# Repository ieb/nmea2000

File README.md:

This repository contains a number of utilities generally aimed at interfacing with a NMEA2000 CAN bus and collecting stats in InfluxDB for analysis in Grafana.

The repository is mainly to keep a record of work in progress, rather than a neat and tidy implementation, but if it helps others, great.

The code runs on an Arduino Due with a CAN bus trancever.
Some code may also run on an Arduino Mega to simulate Raymarine wind, speed and temperature sensors.
The heavy lifting on the Arduino as been done by https://github.com/ttlappalainen/NMEA2000.git to use the code here on a Due you may also need
https://github.com/collin80/due_can.git https://github.com/ttlappalainen/NMEA2000_due.git which the NMEA2000 implementation and CAN Bus drivers for the Due. 

* libs contains c++ code for the ArduinoDue
** batteryMonitor.h - monitoring batteries and current using Hall Effect sensors on ADC pins.
** boarMonitor.h - emitting boat speed, wind speed data as NMEA2000 PGNs
** enviroMonitor.h - monitoring pressure and temperature
** events.h - an event queue.
** monitors.h - constants
** motionSensor.h - rotation, acceleration sensor
** multiSensor.h - wind and water speed sensor with corrections for motion etc, also calculates 
** pogo1250.h - Data for a pogo1250 polar.
** polar.h - polar performance calculations.
** statistics.h - stats for linear and radial data.
** testmocks.h - mocks to allow tests to run.
** waterMonitor.h - water temp sensor.
* monitorAndBridge contains a sensor monitor and bridge from a NMEA2000 bus to ActisenseSerial, with the ability to read the raw signals from Airmar water speed and RayMarine WindSensorts, battery voltages and a 10DoF sensor board. There is a built in polar performance monitor that emits % polar performance and target boat speed.

The Marine instrument installation is a Raymarine SeatalkNG installation with a e7 MFD, althogh there is nothing here that is specific to Raymarine. At the electrical and protocol level SeatalkNG == NMEA2000 == CAN@250kb/s. The differences are physical, mainly to ease installation.

As well as emitting CAM messages onto the NMEA2000 bus the Arduino Due runs code to implement sufficient of the Actisense protocol to feed SignalK running on a Pi Zero W. Installation of that part is listed below. Most of this is achieved with confgiguration and no additional code.

# Pi Zero W installation - Rough notes.

Installation on a Pi Zero W for pushing stats from NMEA2000 -> Arduino Due -> SkignalK -> InfluxDB -> Grafana

Using Raspbain Lite written to a SDMicro card boot and configure the Pi Zero W, once booted. At the console (HDMI+USB Keyboard)

## Setup wifi as root
    
    cat << EOF > /etc/wpa_supplicant/wpa_supplicant.conf 
    country=GB
    ctrl_interface=DIR=/var/run/wpa_supplicant GROUP=netdev
    update_config=1
    network={
         ssid="yourSSID"
         psk="*********"
    }
    EOF

## TODO: setup as a Access Point, assuming it can be done, if not make the MFD the access point and join that network.

## Enable SSH

    raspi-config
    # then enable ssh server

## reboot to get the wifi up.

Now switch to using ssh in from a Linux box.

## install signalK requirements all as root

    apt-get update
    apt-get install -y curl git build-essential libnss-mdns avahi-utils libavahi-compat-libdnssd-dev
    cd /opt/
//    wget https://nodejs.org/dist/v6.10.2/node-v6.10.2-linux-armv6l.tar.xz
    wget https://nodejs.org/dist/v6.11.1/node-v6.11.1-linux-armv6l.tar.gz 
    tar xvzf node-v6.11.1-linux-armv6l.tar.gz  
    rm node-v6.11.1-linux-armv6l.tar.gz 
    cd /usr/local/bin/
    ln -s /opt/node-v6.11.1-linux-armv6l/bin/* .

## Install InfluxDB as root
    cd 
    wget http://ftp.us.debian.org/debian/pool/main/i/influxdb/influxdb_1.1.1+dfsg1-4_armhf.deb
    wget http://ftp.us.debian.org/debian/pool/main/i/influxdb/influxdb-client_1.1.1+dfsg1-4_armhf.deb
    dpkg -i influxdb_1.1.1+dfsg1-4_armhf.deb
    dpkg -i influxdb-client_1.1.1+dfsg1-4_armhf.deb
    apt-get install -f

## Install Grafana as root

    wget https://bintray.com/fg2it/deb-rpi-1b/download_file?file_path=main%2Fg%2Fgrafana_4.2.0_armhf.deb
    mv download_file\?file_path\=main%2Fg%2Fgrafana_4.2.0_armhf.deb grafana_4.2.0_armhf.deb
    dpkg -i grafana_4.2.0_armhf.deb 
    systemctl daemon-reload
    systemctl enable grafana-server
    systemctl start grafana-server

## Install collectd to get stats on the OS into InfluxDB

This will allow you to see if the Pi Zero is overloaded. 

    apt-get install collectd

Edit collectd to disable rrdtool, battery and irq plugins, removing the config sections.
Enable network and add the following

    <Plugin network>
          Server "127.0.0.1" "8096"
    </Plugin>

Edit /etc/influxdb/influxdb.conf to enable collectd

    [[collectd]]
      enabled = true
      bind-address = ":8096"
      database = "collectd"
      typesdb = "/usr/share/collectd/types.db"

Check that /usr/share/collectd/types.db exists  (if not its at https://github.com/collectd/collectd/blob/master/src/types.db)

    service influxdb restart
    service collectd restart

Check all is Ok

    service influxdb status
    service collectd status
    service grafana-server status

## Complete SignalK installation

As a normal user who is a member of the staff group

    cd /usr/local/src
    git clone https://github.com/SignalK/signalk-server-node.git
    cd signalk-server-node
    npm install     # Wait for some time as everything gets installed.
    npm install mdns
    sudo bash rpi-setup.sh

use port 80 to run SignalK see https://github.com/SignalK/signalk-server-node/blob/master/raspberry_pi_installation.md for more detailed info

## Add reporting to InfluxDB

    cd /usr/local/src/signalk-server-node
    npm install https://github.com/sbender9/signalk-to-influxdb
    service signalk restart

check all ok 

    service signalk status 

Then go to http://localhost and configure the influxDB plugn

check all ok again

    service signalk status 

OS level info should now be in the collectd db, create a Grafana datasource pointing to that DB.
See OS Dashboard.json and windDashboard.json for exmaples.

The SignalK process will report to InfluxDB over the http API, which involves 1 POST oepration per report.
This is probably less overhead than reporting using the InfluxDB UDP route, but keep an eye on load average
and IO stats in Grafana (see OSDashboard.json for a Grafana Daskboard on the OS). Also see WindDashboard for 
a Dashboard on AWA etc.

## Connections

The Arduino is connected to the Pi using a USB Cable, the Arduino appears as a USB CDC Serial port at /dev/ttyACM0 which can be opened at 115200 baud. 

lsusb should show

    root@lunacore:/usr/local/src/signalk-server-node# lsusb
    Bus 001 Device 005: ID 2341:003d Arduino SA 
    Bus 001 Device 001: ID 1d6b:0002 Linux Foundation 2.0 root hub
    root@lunacore:/usr/local/src/signalk-server-node# 
    root@lunacore:/usr/local/src/signalk-server-node# usb-devices 

    T:  Bus=01 Lev=00 Prnt=00 Port=00 Cnt=00 Dev#=  1 Spd=480 MxCh= 1
    D:  Ver= 2.00 Cls=09(hub  ) Sub=00 Prot=01 MxPS=64 #Cfgs=  1
    P:  Vendor=1d6b ProdID=0002 Rev=04.04
    S:  Manufacturer=Linux 4.4.50+ dwc_otg_hcd
    S:  Product=DWC OTG Controller
    S:  SerialNumber=20980000.usb
    C:  #Ifs= 1 Cfg#= 1 Atr=e0 MxPwr=0mA
    I:  If#= 0 Alt= 0 #EPs= 1 Cls=09(hub  ) Sub=00 Prot=00 Driver=hub

    T:  Bus=01 Lev=01 Prnt=01 Port=00 Cnt=01 Dev#=  5 Spd=12  MxCh= 0
    D:  Ver= 1.10 Cls=02(commc) Sub=00 Prot=00 MxPS= 8 #Cfgs=  1
    P:  Vendor=2341 ProdID=003d Rev=00.01
    S:  Manufacturer=Arduino (www.arduino.cc)
    S:  Product=Arduino Due Prog. Port
    S:  SerialNumber=9543334393335111B181
    C:  #Ifs= 2 Cfg#= 1 Atr=c0 MxPwr=100mA
    I:  If#= 0 Alt= 0 #EPs= 1 Cls=02(commc) Sub=02 Prot=01 Driver=cdc_acm
    I:  If#= 1 Alt= 0 #EPs= 2 Cls=0a(data ) Sub=00 Prot=00 Driver=cdc_acm
    root@lunacore:/usr/local/src/signalk-server-node# 

Signak node server should be configured with an actisense input listening to this port, and should have plugins configured to 
a) send data to InfluxDB b) NMEA0183. Currently there are only plugins for TCP connections which causes a high level of 
turnover of TCP ports, it might be better to use UDP, that that will need some coding.

It is possible to power the Pi from the ArduinoDue over USB and visa versa. The Arduino uses < 100mA, but the Pi might use a bit more when under full load. 

# Update - September 2017

Sending data to influxDB on a standard SignalK setup swamps InfluxDB making it unusable, probably as a result of the frequency of packets > 1s in some cases, and the way the standard signalk-to-influxDB plugin is written. New signalk-telemetry plugin dixes this sending data in one block, queued to be more effcient at a fixed rate.

It may be possible to run everything from the Pi using socketCan rather than using a Due. This needs MCP2515 trancevers, 12C for the 10Dof sensor. In addition 1Wire temperature sensors and a I2C RTC can be added. Potentially this reduces power consumption as 80mA isnt needed to power the Due any more. the Pi has no A2D so a SPI based chip would need to be used.

The Pi supports 2x CAN trancevers with SocketCAN.

Raspberry Pi 10Dof

The npm module https://www.npmjs.com/package/nodeimu works for several 10DOf sensors on i2C, setup only requires i2c is enabled.
The IMU Requires configuration see https://github.com/RTIMULib/RTIMULib2 which also requires Octave to be installed for full calibration.

dtparam=i2c_arm=on

Raspberry Pi RTC
Disconnected from ntp the Pi will not keep time, using a ds3231 over i2c gives acurate time once setup.

dtoverlay=i2c-rtc,ds3231
see http://raspmer.blogspot.co.uk/2015/07/how-to-use-ds3231-i2c-real-time-clock.html

Raspberry Pi 1 Wire

DS18B20 are 1 wire temperature sensors. To read on a Pi enable 1wire and connedt with a 4K7 pullup to 3.3v, where the 1 wire is the default pin 7 

Output is at cat  /sys/bus/w1/devices/<ID>/w1_slave.
Map the ID to the sensor by warming each sensor in turn.

https://www.npmjs.com/package/ds18b20 for NPM

Raspberry Pi CanBus

Investigating how to run over SocketCan

2x MCP2515 drivers with Trancevers from eBay, MUST be connected with 3.3V to 5V level shifters to avoid GPIO damage as the trancevers will run at 5V. 2 can be connected to get CAN0 and CAN1

Wiring 

    2 5V   --------------- Vdd
    1 3V3   ------> LS 3V3
    2 5V ---------> LS 5V
    9 GND --------> LS GND
    9 GND  --------------  GND
    19 MOSI ---->  LS ----> SI0 & SI1
    21 MOSO <----  LS <---- SO0 & SO1
    23 SCLK ------> LS ----> SCLK0 & SCLK1
    24 CE0 ------> LS ----> CS0
    26 CE1 ------> LS ----> CS1
    18 GPIO24 <--  LS <---- INT0
    22 xGPIO25 <--  LS <---- INT1

    dtoverlay mcp2515-can0  oscillator=8000000 interrupt=24
    dtoverlay mcp2515-can1  oscillator=8000000 interrupt=25

    root@raspb:~/can-utils# dmesg | egrep "spi|can"
    [  477.594591] mcp251x spi0.0 can0: MCP2515 successfully initialized.
    [  487.165293] mcp251x spi0.1 can1: MCP2515 successfully initialized.
    [  495.704786] can: controller area network core (rev 20120528 abi 9)
    root@raspb:~/can-utils# ifconfig can0
    can0: flags=128<NOARP>  mtu 16
            unspec 00-00-00-00-00-00-00-00-00-00-00-00-00-00-00-00  txqueuelen 10  (UNSPEC)
            RX packets 0  bytes 0 (0.0 B)
            RX errors 0  dropped 0  overruns 0  frame 0
            TX packets 0  bytes 0 (0.0 B)
            TX errors 0  dropped 0 overruns 0  carrier 0  collisions 0

    root@raspb:~/can-utils# ifconfig can1
    can1: flags=128<NOARP>  mtu 16
            unspec 00-00-00-00-00-00-00-00-00-00-00-00-00-00-00-00  txqueuelen 10  (UNSPEC)
            RX packets 0  bytes 0 (0.0 B)
            RX errors 0  dropped 0  overruns 0  frame 0
            TX packets 0  bytes 0 (0.0 B)
            TX errors 0  dropped 0 overruns 0  carrier 0  collisions 0

    root@raspb:~/can-utils# 

Install can-utils from source.

    # git clone https://github.com/linux-can/can-utils.git
    # cd can-utils
    # ./autogen.sh
    # ./configure
    # make
    # sudo make install

If initialisation reports a wiring problem, then there almost cerainly is a wiring problem.

Configure interface

    root@raspb:~/can-utils# ip link set can0 up type can bitrate 250000
    root@raspb:~/can-utils#  ip link set can1 up type can bitrate 250000

Test

    root@raspb:~/can-utils# ./candump can1 &
    [1]+ ./candump can1 &
    root@raspb:~/can-utils# ./cansend can0 001#1122334455667788
      can1  001   [8]  11 22 33 44 55 66 77 88
    root@raspb:~/can-utils# ./cansend can0 001#1122334455667788
      can1  001   [8]  11 22 33 44 55 66 77 88
    root@raspb:~/can-utils# ./cansend can0 001#1122334455667788
      can1  001   [8]  11 22 33 44 55 66 77 88
    root@raspb:~/can-utils# 

To echo all CAN1 traffic to CAN0, setup CAN1 to listen only, and setup CAN0 to have loopback enabled to anything reading CAN0 gets the CAN0 messages as well.

    root@raspb:~/can-utils# ip link set can0 up type can bitrate 250000 loopback on
    root@raspb:~/can-utils#  ip link set can1 up type can bitrate 250000 listen-only on

Then to bridge

    candump can1 -B can0

For can0 -> SK

see https://github.com/chacal/signalk-socketcan-device

------------------------------------------------------

Moved back to the Due for now as its single threaded and doesnt stop expecially with no memory allocation. Processing power is a lot less, but it does a lot less also, not having an OS. 84MHz is plenty for this usage.

Todo:
Test polar calcs - partially done.
Test Can0 - done
Test IMU and calibrate - done.
Test Cos and Sin - done
Test Pulse counters  - done
Test SD card
Test 1 Wire
Test wind and speed calcs
Test linear voltage regulator vs noise from dc-dc converter 
   Linear voltage is no nose, but too hot
   LTSpice model indicates a 10uF cap will eliminate ripple from buck converter.

Input is candump can0 pipe, output is signalk-socketcan-device.

    "pipedProviders": [{
      "id": "can0",
      "pipeElements": [
        {
          "type": "providers/execute",
          "options": {
            "command": "candump can0 | candump2analyzer | analyzer -json -si -nv"
          }
        },
        {
          "type": "providers/liner"
        },
        {
          "type": "providers/from_json"
        },
        {
          "type": "signalk-socketcan-device",
          "options": {
            "n2kAddress": 110,
            "canDevice": "can0"
          }
        },
        {
          "type": "providers/n2k-signalk"
        }
      ]
    }]

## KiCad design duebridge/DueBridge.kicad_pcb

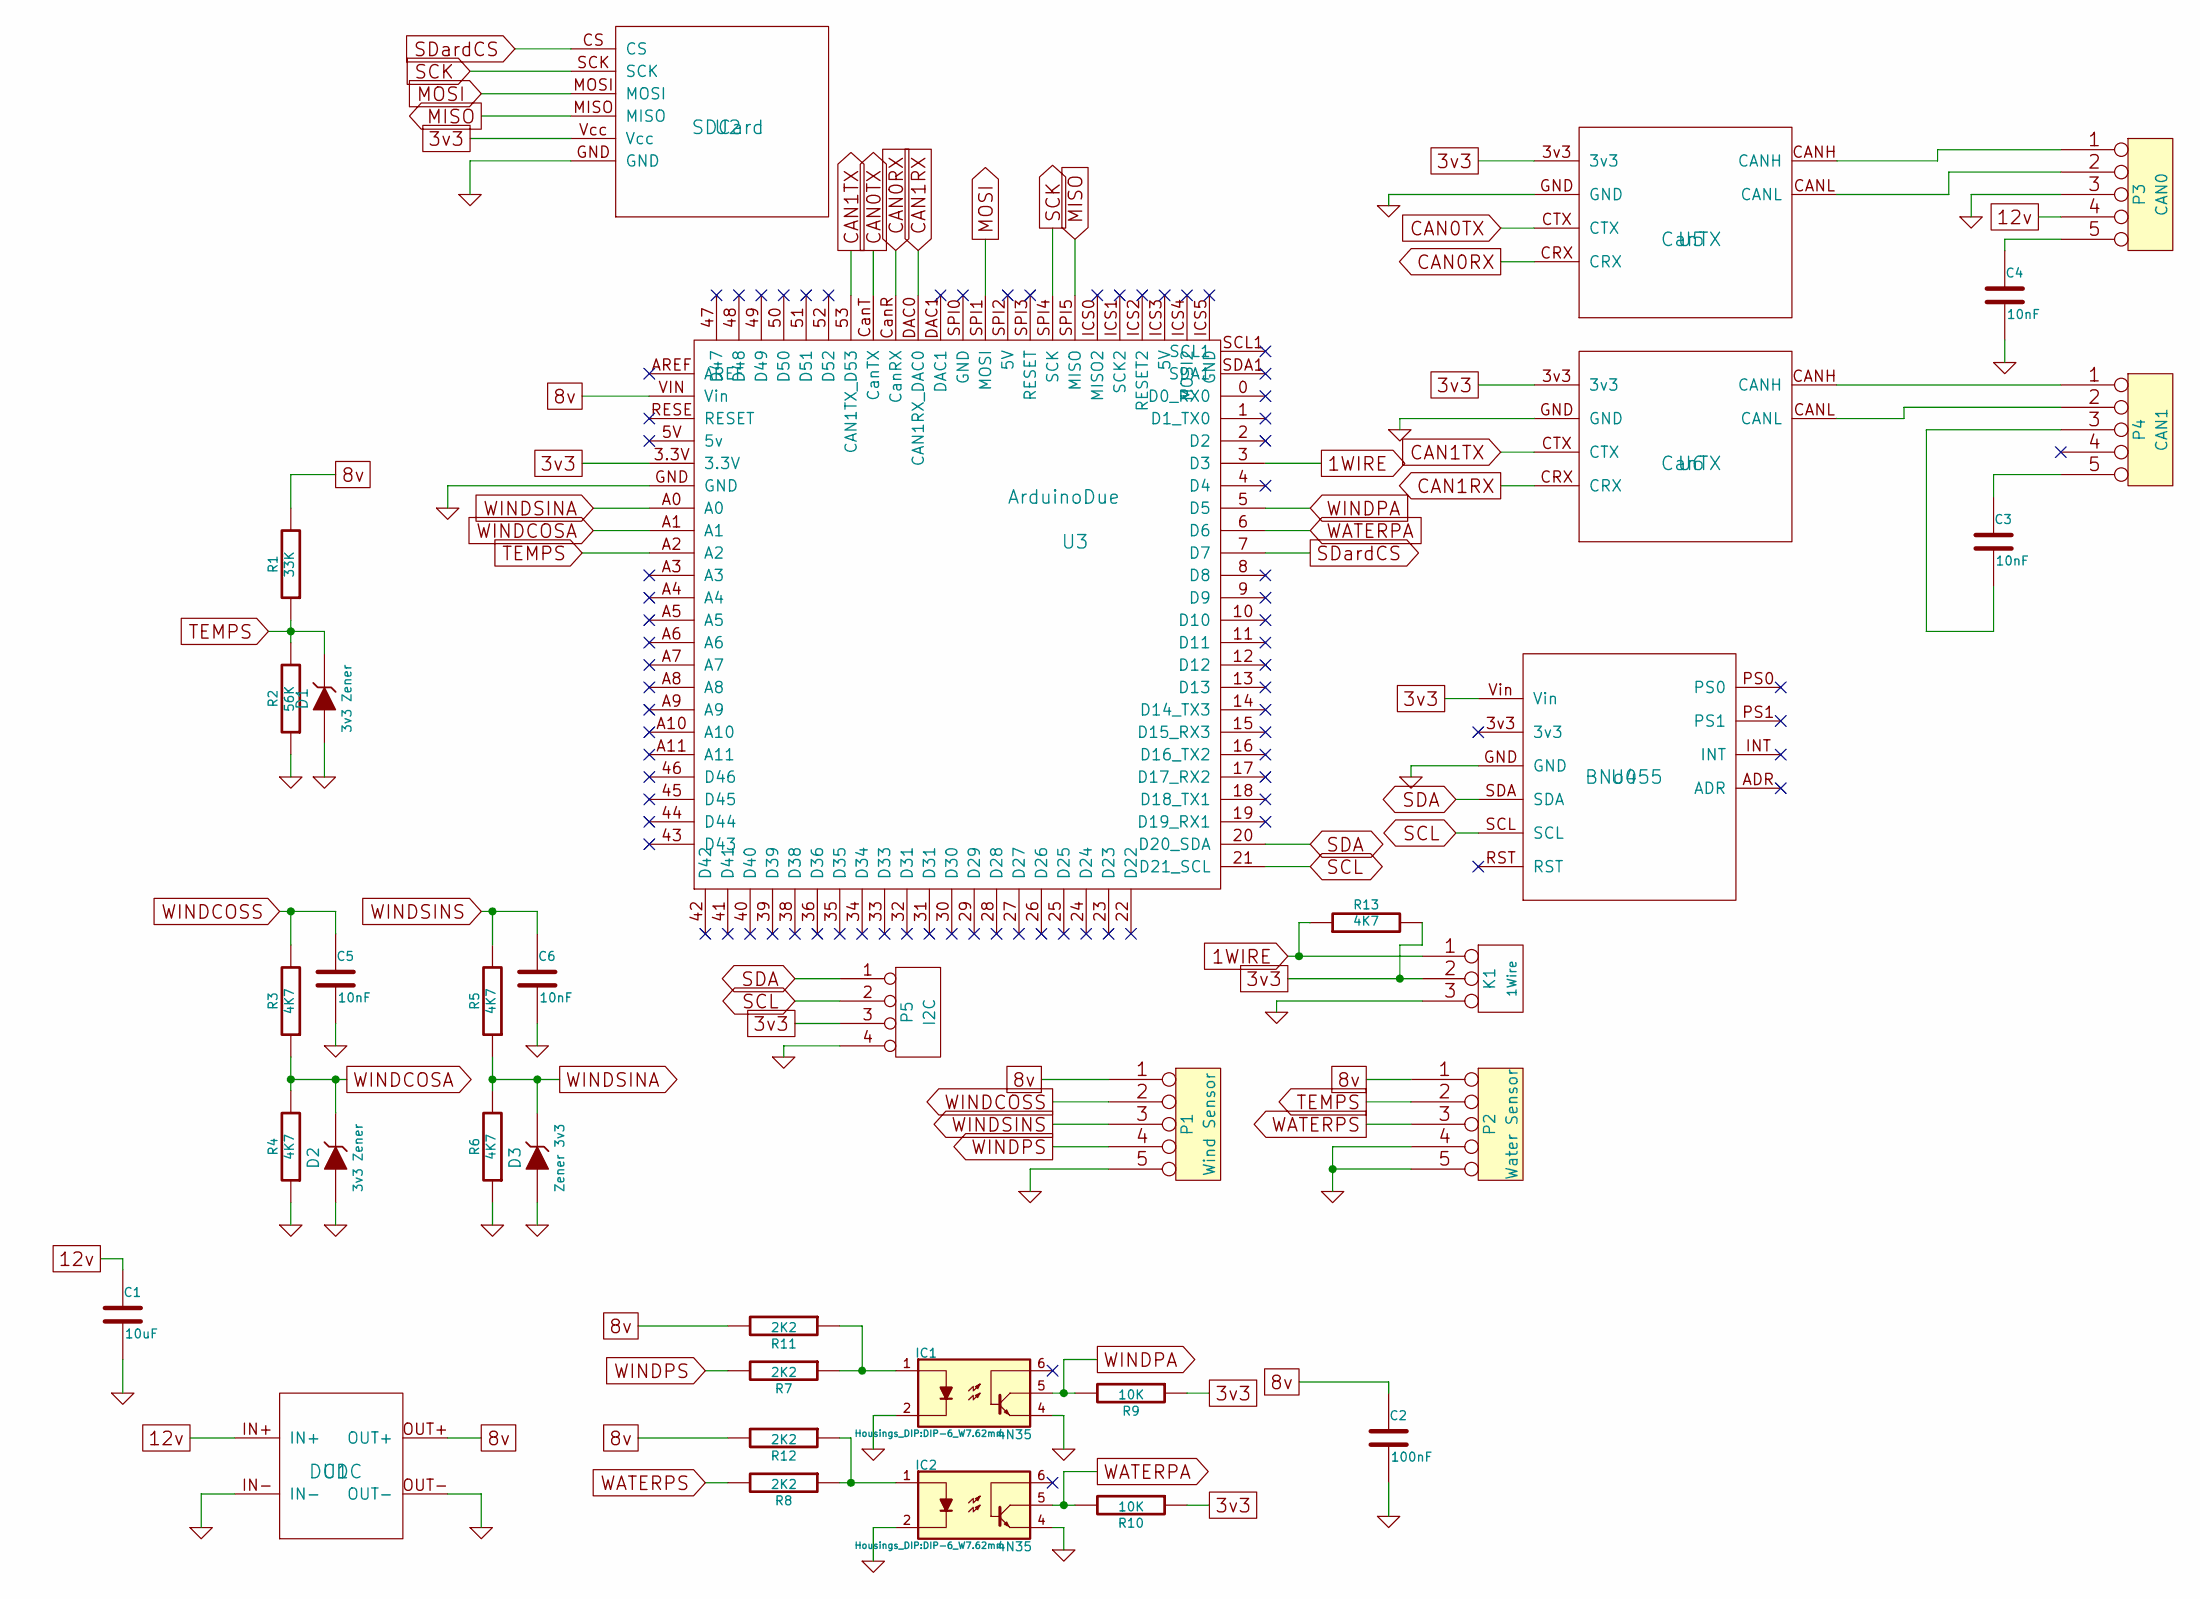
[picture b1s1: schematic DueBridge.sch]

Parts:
C1: 10uF; C_Radial_D10_L13_P5
C2: 100nF; C_Disc_D7.5_P5
C3, C4, C5, C6: 10nF; C_Disc_D7.5_P5
D1, D2: 3v3 Zener; Resistor_Horizontal_RM7mm
D3: Zener 3v3; Resistor_Horizontal_RM7mm
IC1, IC2: 4N35; DIP-6_W7.62mm
K1: 1Wire; Pin_Header_Straight_1x03
P1: Wind Sensor; bornier5
P2: Water Sensor; bornier5
P3: CAN0; CanCon
P4: CAN1; CanCon
P5: I2C; Pin_Header_Straight_1x04
R1: 33K; Resistor_Horizontal_RM7mm
R2: 56K; Resistor_Horizontal_RM7mm
R3, R4, R5, R6, R13: 4K7; Resistor_Horizontal_RM7mm
R7, R8, R11, R12: 2K2; Resistor_Horizontal_RM7mm
R9, R10: 10K; Resistor_Horizontal_RM7mm
U1: DCDC
U2: SDCard
U3: ArduinoDue; Arduino_Mega_Due
U4: BNo055
U5, U6: CanTX; CanTrans

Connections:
1WIRE: K1.1, R13.1, U3.3 (D3)
3v3: K1.2 (PM), P5.3, R9.1, R10.1, R13.2, U2.Vcc, U3.3.3V, U4.Vin, U5.3v3, U6.3v3
8v: C2.1, P1.1, P2.1, R1.2, R11.2, R12.2, U1.OUT+, U3.VIN (Vin)
12v: C1.1, P3.4, U1.IN+
CAN0RX: U3.CanR (CanRX), U5.CRX
CAN0TX: U3.CanT (CanTX), U5.CTX
CAN1RX: U3.DAC0 (CAN1RX_DAC0), U6.CRX
CAN1TX: U3.53 (CAN1TX_D53), U6.CTX
GND: C1.2, C2.2, C4.2, C5.2, C6.2, D1.1 (A), D2.1 (A), D3.1 (A), IC1.2, IC1.4, IC2.2, IC2.4, K1.3, P1.5, P2.4, P2.5, P3.3, P5.4, R2.1, R4.1, R6.1, U1.IN-, U1.OUT-, U2.GND, U3.GND, U4.GND, U5.GND, U6.GND
MISO: U2.MISO, U3.SPI5 (MISO)
MOSI: U2.MOSI, U3.SPI1 (MOSI)
unnamed: C3.1, P4.5
unnamed: C3.2, P4.3
unnamed: C4.1, P3.5
unnamed: IC1.1, R7.1, R11.1
unnamed: IC2.1, R8.1, R12.1
unnamed: P3.1, U5.CANH
unnamed: P3.2, U5.CANL
unnamed: P4.1, U6.CANH
unnamed: P4.2, U6.CANL
SCK: U2.SCK, U3.SPI4 (SCK)
SCL: P5.2, U3.21 (D21_SCL), U4.SCL
SDA: P5.1, U3.20 (D20_SDA), U4.SDA
SDardCS: U2.CS, U3.7 (D7)
TEMPS: D1.2 (K), P2.2, R1.1, R2.2, U3.A2
WATERPA: IC2.5, R10.2, U3.6 (D6)
WATERPS: P2.3, R8.2
WINDCOSA: D2.2 (K), R3.1, R4.2, U3.A1
WINDCOSS: C5.1, P1.2, R3.2
WINDPA: IC1.5, R9.2, U3.5 (D5)
WINDPS: P1.4, R7.2
WINDSINA: D3.2 (K), R5.1, R6.2, U3.A0
WINDSINS: C6.1, P1.3, R5.2

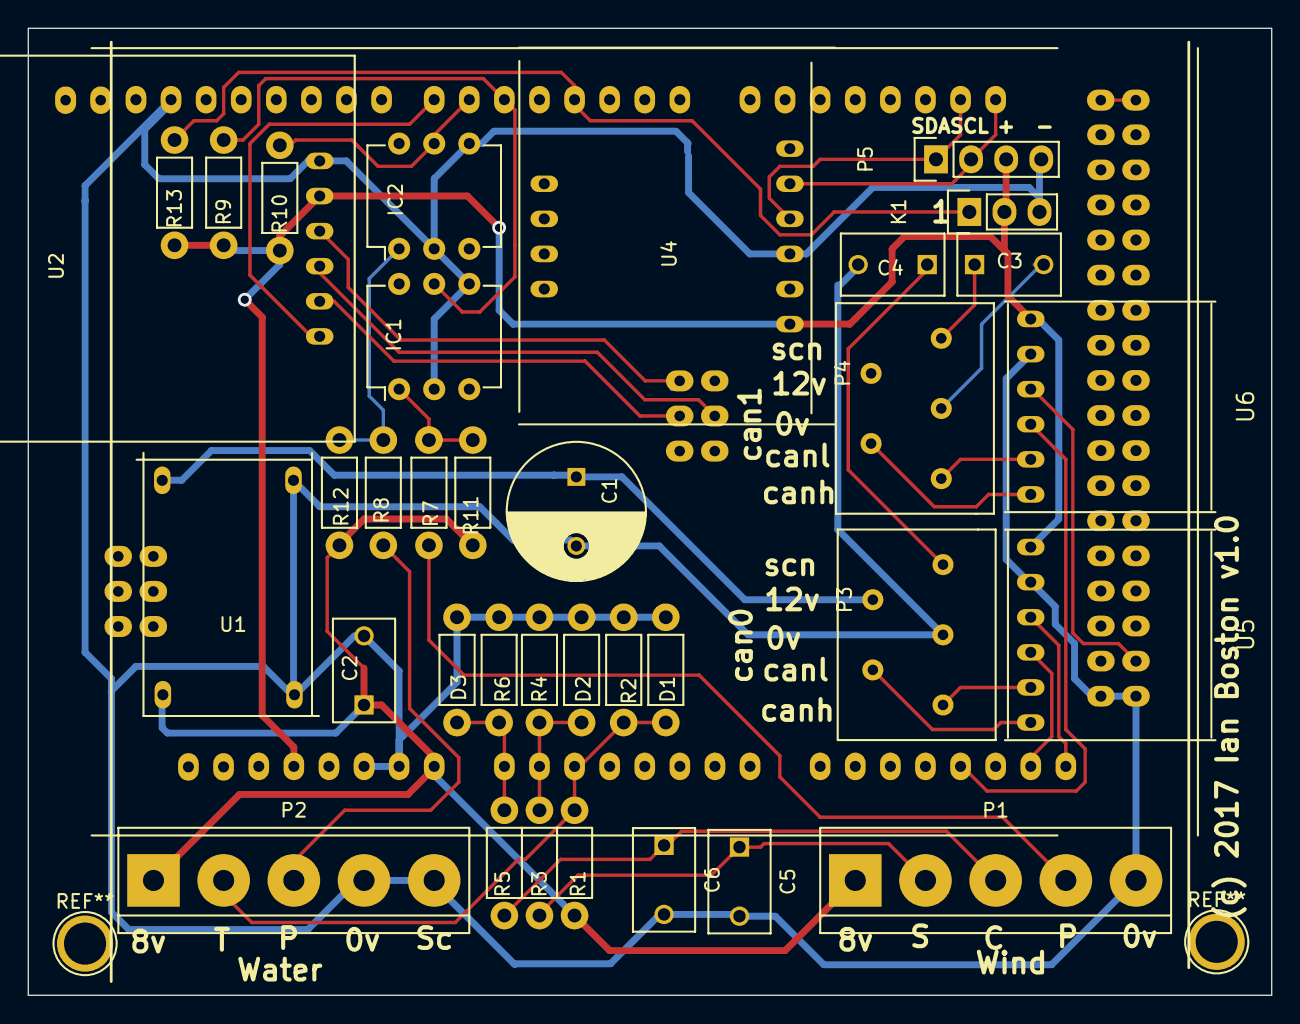
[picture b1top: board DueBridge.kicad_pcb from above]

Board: 2 copper layers, 90.0 x 70.0 mm, 36 parts (0 on the bottom side), 33 nets.

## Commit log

2017-03-16 Initial commit of monitoring code
2017-04-09 Added various monitors and supporting libraries
2017-04-09 Updated readme and added basic wind dashboard
2017-04-09 Added influxDB and collectd conf files
2017-04-09 Moved config
2017-04-09 Added transducer simulation
2017-04-09 Fixed buid on monitorAndBridge
2017-04-15 Added Simulation schema for reference
2017-06-10 Working version sending data to STNg network, fixed many issues with sending data.
2017-07-16 Much improved version
2017-07-20 Update adding some tests
2017-09-05 Running version used over 08/2017, adds ability to configure over serial + some fixes
2017-12-05 Moved to using a BNo055 and largely rewritten with a new board
2017-12-11 Tested pulse sensors, and basic PGN output.

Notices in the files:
duebridge/DueBridge.kicad_pcb:
(c) 2017 Ian Boston v1.0
